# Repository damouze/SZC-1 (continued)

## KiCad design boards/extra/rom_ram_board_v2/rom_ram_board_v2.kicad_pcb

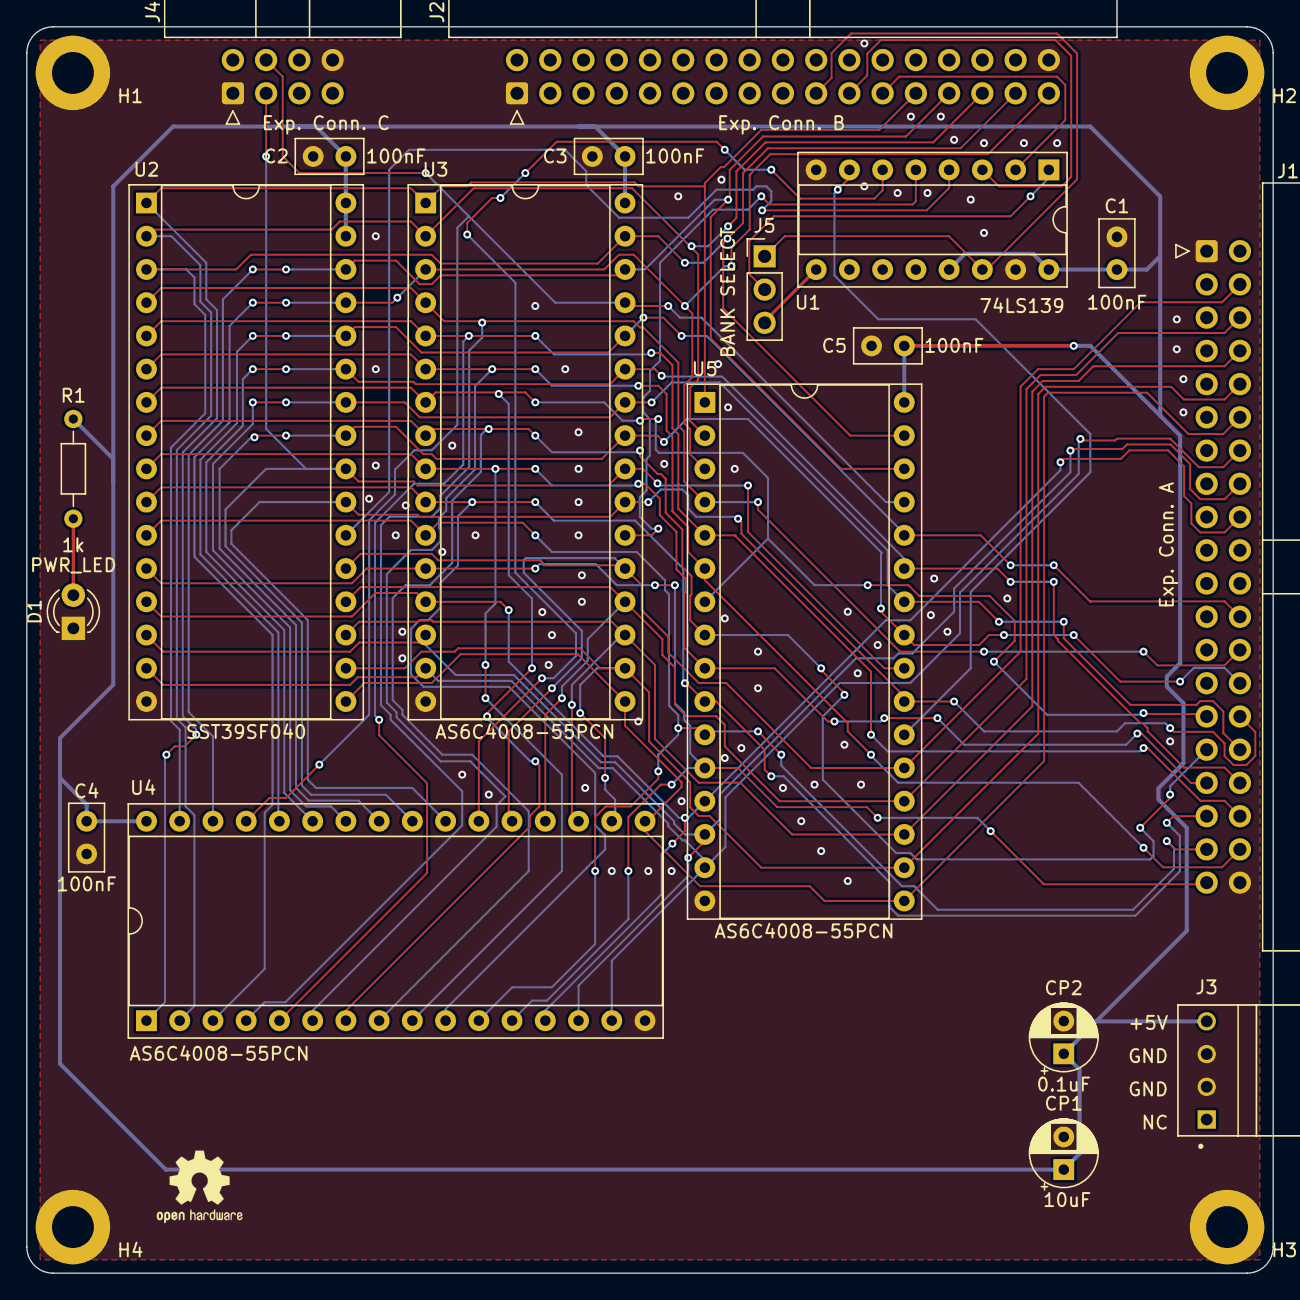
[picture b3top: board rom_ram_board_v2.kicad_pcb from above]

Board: 2 copper layers, 95.2 x 95.2 mm, 23 parts (0 on the bottom side), 41 nets.

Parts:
C1, C2, C3, C4, C5: 100nF; C_Disc_D5.0mm_W2.5mm_P2.50mm
CP1: 10uF; CP_Radial_D5.0mm_P2.50mm
CP2: 0.1uF; CP_Radial_D5.0mm_P2.50mm
D1: PWR_LED; LED_D3.0mm
H1, H2, H3, H4: MountingHole_Pad; MountingHole_3.2mm_M3_ISO7380_Pad
J1: Exp. Conn. A; IDC-Header_2x20_P2.54mm_Horizontal
J2: Exp. Conn. B; IDC-Header_2x17_P2.54mm_Horizontal
J3: Power; TE_171826-4
J4: Exp. Conn. C; IDC-Header_2x04_P2.54mm_Horizontal
J5: BANK SELECT; PinHeader_1x03_P2.54mm_Vertical
R1: 1k; R_Axial_DIN0204_L3.6mm_D1.6mm_P7.62mm_Horizontal
U1: 74LS139; DIP-16_W7.62mm_Socket
U2: SST39SF040; DIP-32_W15.24mm_Socket
U3, U4, U5: AS6C4008-55PCN; DIP-32_W15.24mm_Socket

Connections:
/+5V: C1.1, C2.1, C3.1, C4.1, C5.1, CP1.1, CP2.1, J3.4, R1.1, U1.13 (A1), U1.16 (VCC), U2.31 (PGM), U2.32 (VCC), U3.32 (VCC), U4.32 (VCC), U5.32 (VCC)
/B_A0: J1.39, U2.12 (A0), U3.12 (A0), U4.12 (A0), U5.12 (A0)
/B_A1: J1.37, U2.11 (A1), U3.11 (A1), U4.11 (A1), U5.11 (A1)
/B_A2: J1.35, U2.10 (A2), U3.10 (A2), U4.10 (A2), U5.10 (A2)
/B_A3: J1.33, U2.9 (A3), U3.9 (A3), U4.9 (A3), U5.9 (A3)
/B_A4: J1.31, U2.8 (A4), U3.8 (A4), U4.8 (A4), U5.8 (A4)
/B_A5: J1.29, U2.7 (A5), U3.7 (A5), U4.7 (A5), U5.7 (A5)
/B_A6: J1.38, U2.6 (A6), U3.6 (A6), U4.6 (A6), U5.6 (A6)
/B_A7: J1.36, U2.5 (A7), U3.5 (A7), U4.5 (A7), U5.5 (A7)
/B_A8: J1.34, U2.27 (A8), U3.27 (A8), U4.27 (A8), U5.27 (A8)
/B_A9: J1.32, U2.26 (A9), U3.26 (A9), U4.26 (A9), U5.26 (A9)
/B_A10: J1.30, U2.23 (A10), U3.23 (A10), U4.23 (A10), U5.23 (A10)
/B_A11: J1.28, U2.25 (A11), U3.25 (A11), U4.25 (A11), U5.25 (A11)
/B_A12: J1.26, U2.4 (A12), U3.4 (A12), U4.4 (A12), U5.4 (A12)
/B_A13: J1.24, U2.28 (A13), U3.28 (A13), U4.28 (A13), U5.28 (A13)
/B_D0: J1.18, U2.13 (D0), U3.13 (DQ0), U4.13 (DQ0), U5.13 (DQ0)
/B_D1: J1.16, U2.14 (D1), U3.14 (DQ1), U4.14 (DQ1), U5.14 (DQ1)
/B_D2: J1.14, U2.15 (D2), U3.15 (DQ2), U4.15 (DQ2), U5.15 (DQ2)
/B_D3: J1.12, U2.17 (D3), U3.17 (DQ3), U4.17 (DQ3), U5.17 (DQ3)
/B_D4: J1.10, U2.18 (D4), U3.18 (DQ4), U4.18 (DQ4), U5.18 (DQ4)
/B_D5: J1.8, U2.19 (D5), U3.19 (DQ5), U4.19 (DQ5), U5.19 (DQ5)
/B_D6: J1.6, U2.20 (D6), U3.20 (DQ6), U4.20 (DQ6), U5.20 (DQ6)
/B_D7: J1.4, U2.21 (D7), U3.21 (DQ7), U4.21 (DQ7), U5.21 (DQ7)
/GND: C1.2, C2.2, C3.2, C4.2, C5.2, CP1.2, CP2.2, D1.1 (K), H1.1, H2.1, H3.1, H4.1, J1.1, J1.40, J2.1, J2.34, J3.2, J3.3, J4.1, J4.8, U1.8 (GND), U1.15 (E), U2.16 (GND), U3.16 (VSS), U4.16 (VSS), U5.16 (VSS)
/M_A14: J2.33, U2.29 (A14), U3.3 (A14), U4.3 (A14), U5.3 (A14)
/M_A15: J2.31, U2.3 (A15), U3.31 (A15), U4.31 (A15), U5.31 (A15)
/M_A16: J2.29, U2.2 (A16), U3.2 (A16), U4.2 (A16), U5.2 (A16)
/M_A17: J2.27, U2.30 (A17), U3.30 (A17), U4.30 (A17), U5.30 (A17)
/M_A18: J2.25, U2.1 (A18), U3.1 (A18), U4.1 (A18), U5.1 (A18)
/M_A19: J2.23, U1.2 (A0)
/M_A20: J2.21, U1.3 (A1)
/M_A21: J2.19, J5.1, U1.14 (A0)
/~BANK_ENABLE: J5.2, U1.1 (E)
/~MA_21: J5.3, U1.9 (O3)
/~MEMR: J4.3, U2.24 (OE), U3.24 (OE#), U4.24 (OE#), U5.24 (OE#)
/~MEMW: J4.4, U3.29 (WE#), U4.29 (WE#), U5.29 (WE#)
/~MEM_CS1: U1.4 (O0), U2.22 (CE)
/~MEM_CS2: U1.5 (O1), U3.22 (CE#)
/~MEM_CS3: U1.6 (O2), U4.22 (CE#)
/~MEM_CS4: U1.7 (O3), U5.22 (CE#)
unnamed: D1.2 (A), R1.2

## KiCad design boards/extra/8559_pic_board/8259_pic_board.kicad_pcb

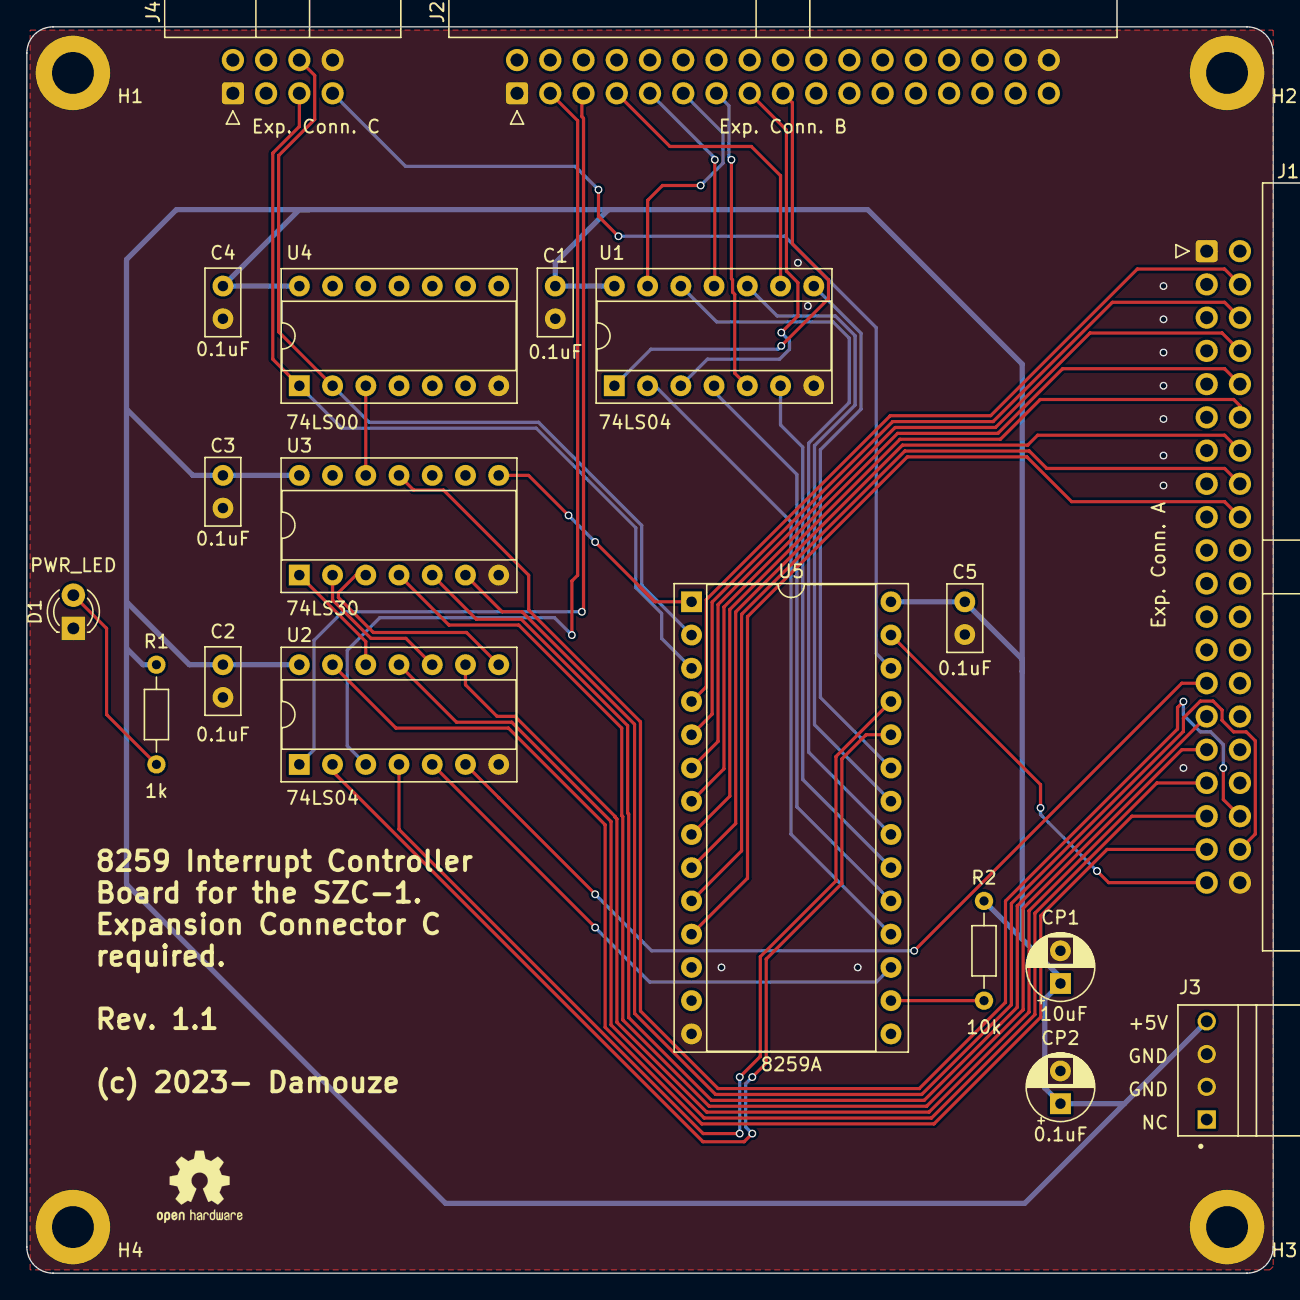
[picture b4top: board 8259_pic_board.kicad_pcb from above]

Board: 2 copper layers, 95.2 x 95.2 mm, 23 parts (0 on the bottom side), 46 nets.

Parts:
C1, C2, C3, C4, C5: 0.1uF; C_Disc_D5.0mm_W2.5mm_P2.50mm
CP1: 10uF; CP_Radial_D5.0mm_P2.50mm
CP2: 0.1uF; CP_Radial_D5.0mm_P2.50mm
D1: PWR_LED; LED_D3.0mm
H1, H2, H3, H4: MountingHole_Pad; MountingHole_3.2mm_M3_ISO7380_Pad
J1: Exp. Conn. A; IDC-Header_2x20_P2.54mm_Horizontal
J2: Exp. Conn. B; IDC-Header_2x17_P2.54mm_Horizontal
J3: Power; TE_171826-4
J4: Exp. Conn. C; IDC-Header_2x04_P2.54mm_Horizontal
R1: 1k; R_Axial_DIN0204_L3.6mm_D1.6mm_P7.62mm_Horizontal
R2: 10k; R_Axial_DIN0204_L3.6mm_D1.6mm_P7.62mm_Horizontal
U1, U2: 74LS04; DIP-14_W7.62mm_Socket
U3: 74LS30; DIP-14_W7.62mm_Socket
U4: 74LS00; DIP-14_W7.62mm_Socket
U5: 8259A; DIP-28_W15.24mm_Socket

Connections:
/+5V: C1.1, C2.1, C3.1, C4.1, C5.1, CP1.1, CP2.1, J3.4, R1.1, R2.2, U1.14 (VCC), U2.14 (VCC), U3.14 (VCC), U4.14 (VCC), U5.28 (VCC)
/B_A0: J1.39, U5.27 (A0)
/B_A1: J1.37, U2.13
/B_A2: J1.35, U2.11
/B_A3: J1.33, U2.9
/B_A4: J1.31, U3.4
/B_A5: J1.29, U3.5
/B_A6: J1.38, U3.6
/B_A7: J1.36, U3.11
/B_D0: J1.18, U5.11 (D0)
/B_D1: J1.16, U5.10 (D1)
/B_D2: J1.14, U5.9 (D2)
/B_D3: J1.12, U5.8 (D3)
/B_D4: J1.10, U5.7 (D4)
/B_D5: J1.8, U5.6 (D5)
/B_D6: J1.6, U5.5 (D6)
/B_D7: J1.4, U5.4 (D7)
/CPU_INT: U2.5, U5.17 (INT)
/GND: C1.2, C2.2, C3.2, C4.2, C5.2, CP1.2, CP2.2, D1.1 (K), H1.1, H2.1, H3.1, H4.1, J1.1, J1.40, J2.1, J2.34, J3.2, J3.3, J4.1, J4.8, U1.7 (GND), U2.7 (GND), U3.7 (GND), U4.7 (GND), U5.14 (GND)
/INT0: U1.2, U5.18 (IR0)
/INT1: U1.4, U5.19 (IR1)
/INT2: U1.6, U5.20 (IR2)
/INT3: U1.12, U5.21 (IR3)
/INT4: U1.10, U5.22 (IR4)
/INT5: U1.8, U5.23 (IR5)
/INT6: U2.2, U5.24 (IR6)
/INT7: U2.4, U5.25 (IR7)
/~BA_1: U2.12, U3.1
/~BA_2: U2.10, U3.2
/~BA_3: U2.8, U3.3
/~INT0: J2.17, U1.1
/~INT1: J2.15, U1.3
/~INT2: J2.13, U1.5
/~INT3: J2.11, U1.13
/~INT4: J2.9, U1.11
/~INT5: J2.7, U1.9
/~INT6: J2.5, U2.1
/~INT7: J2.3, U2.3
/~INTA: J4.7, U5.26 (~INTA)
/~INT: J1.27, U2.6
/~IOR: J4.5, U4.1, U5.3 (~RD)
/~IOW: J4.6, U4.2, U5.2 (~WR)
/~IOXS: U3.12, U4.3
/~PIC_CS: U3.8, U5.1 (~CS)
/~PIC_PLUP: R2.1, U5.16 (~SP/~EN)
unnamed: D1.2 (A), R1.2

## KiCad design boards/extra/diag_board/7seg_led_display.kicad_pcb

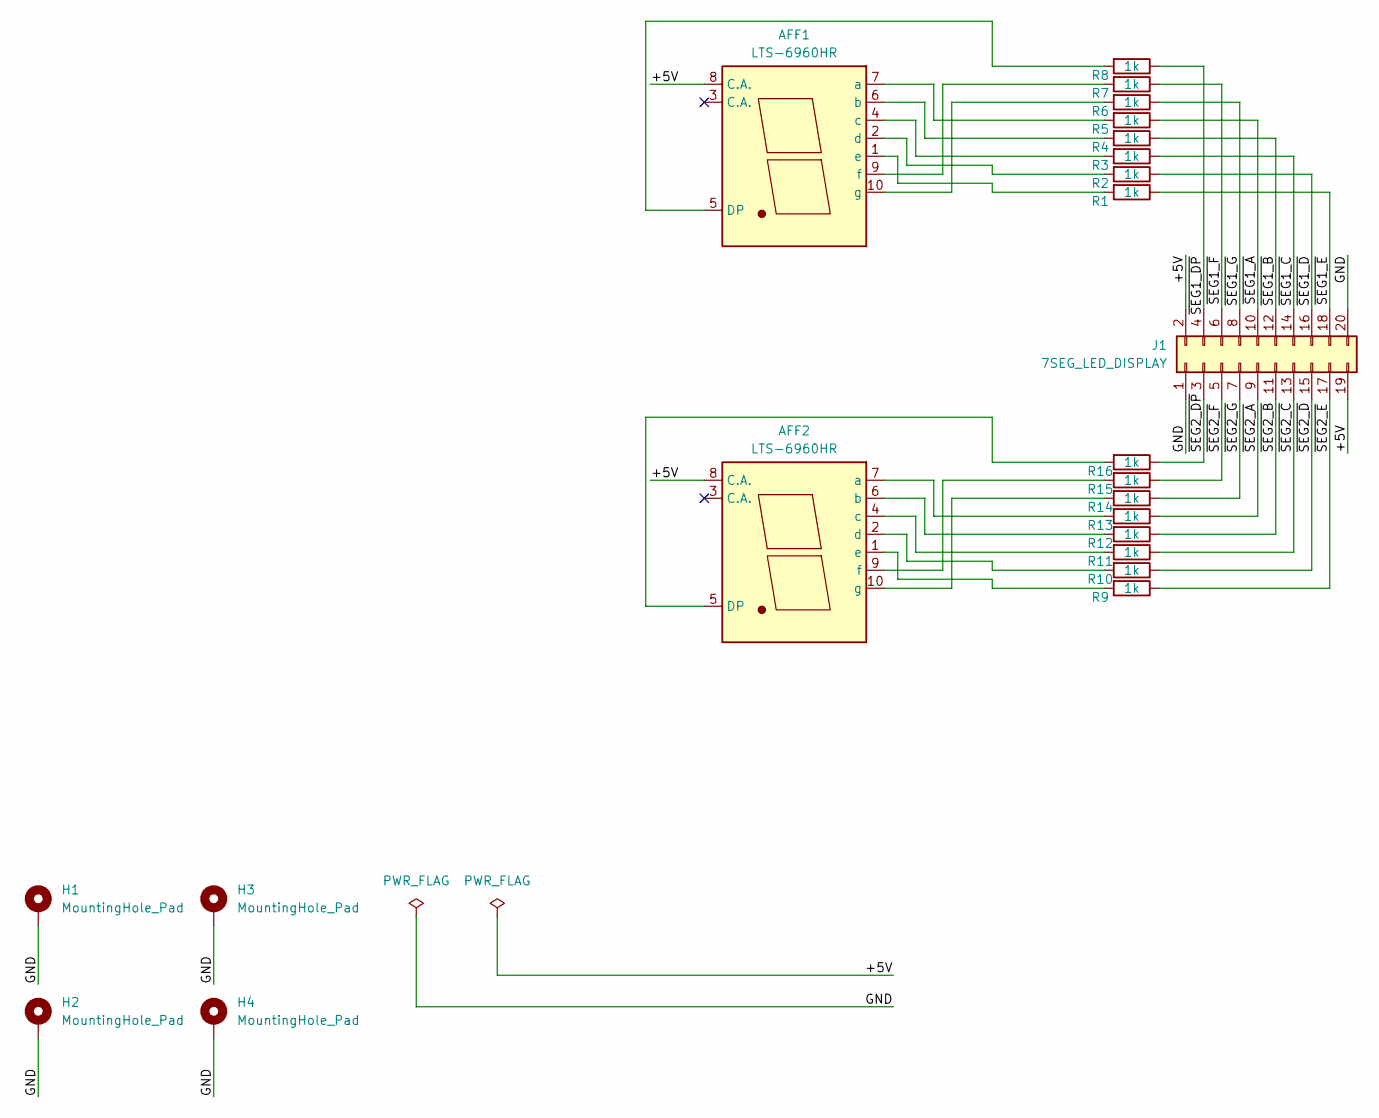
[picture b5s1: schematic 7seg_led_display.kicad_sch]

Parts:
AFF1, AFF2: LTS-6960HR; 7SegmentLED_LTS6760_LTS6780
H1, H2, H3, H4: MountingHole_Pad; MountingHole_3.2mm_M3_ISO7380_Pad
J1: 7SEG_LED_DISPLAY; PinSocket_2x10_P2.54mm_Vertical
R1, R2, R3, R4, R5, R6, R7, R8, R9, R10, R11, R12, R13, R14, R15, R16: 1k; R_Axial_DIN0204_L3.6mm_D1.6mm_P7.62mm_Horizontal

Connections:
/+5V: AFF1.8 (C.A.), AFF2.8 (C.A.), J1.2, J1.19
/GND: H1.1, H2.1, H3.1, H4.1, J1.1, J1.20
/~SEG1_A: J1.10, R5.1
/~SEG1_B: J1.12, R4.1
/~SEG1_C: J1.14, R3.1
/~SEG1_DP: J1.4, R8.1
/~SEG1_D: J1.16, R2.1
/~SEG1_E: J1.18, R1.1
/~SEG1_F: J1.6, R7.1
/~SEG1_G: J1.8, R6.1
/~SEG2_A: J1.9, R13.1
/~SEG2_B: J1.11, R12.1
/~SEG2_C: J1.13, R11.1
/~SEG2_DP: J1.3, R16.1
/~SEG2_D: J1.15, R10.1
/~SEG2_E: J1.17, R9.1
/~SEG2_F: J1.5, R15.1
/~SEG2_G: J1.7, R14.1
unnamed: AFF1.5 (DP), R8.2
unnamed: AFF1.7 (a), R5.2
unnamed: AFF1.6 (b), R4.2
unnamed: AFF1.4 (c), R3.2
unnamed: AFF1.2 (d), R2.2
unnamed: AFF1.1 (e), R1.2
unnamed: AFF1.9 (f), R7.2
unnamed: AFF1.10 (g), R6.2
unnamed: AFF2.5 (DP), R16.2
unnamed: AFF2.7 (a), R13.2
unnamed: AFF2.6 (b), R12.2
unnamed: AFF2.4 (c), R11.2
unnamed: AFF2.2 (d), R10.2
unnamed: AFF2.1 (e), R9.2
unnamed: AFF2.9 (f), R15.2
unnamed: AFF2.10 (g), R14.2

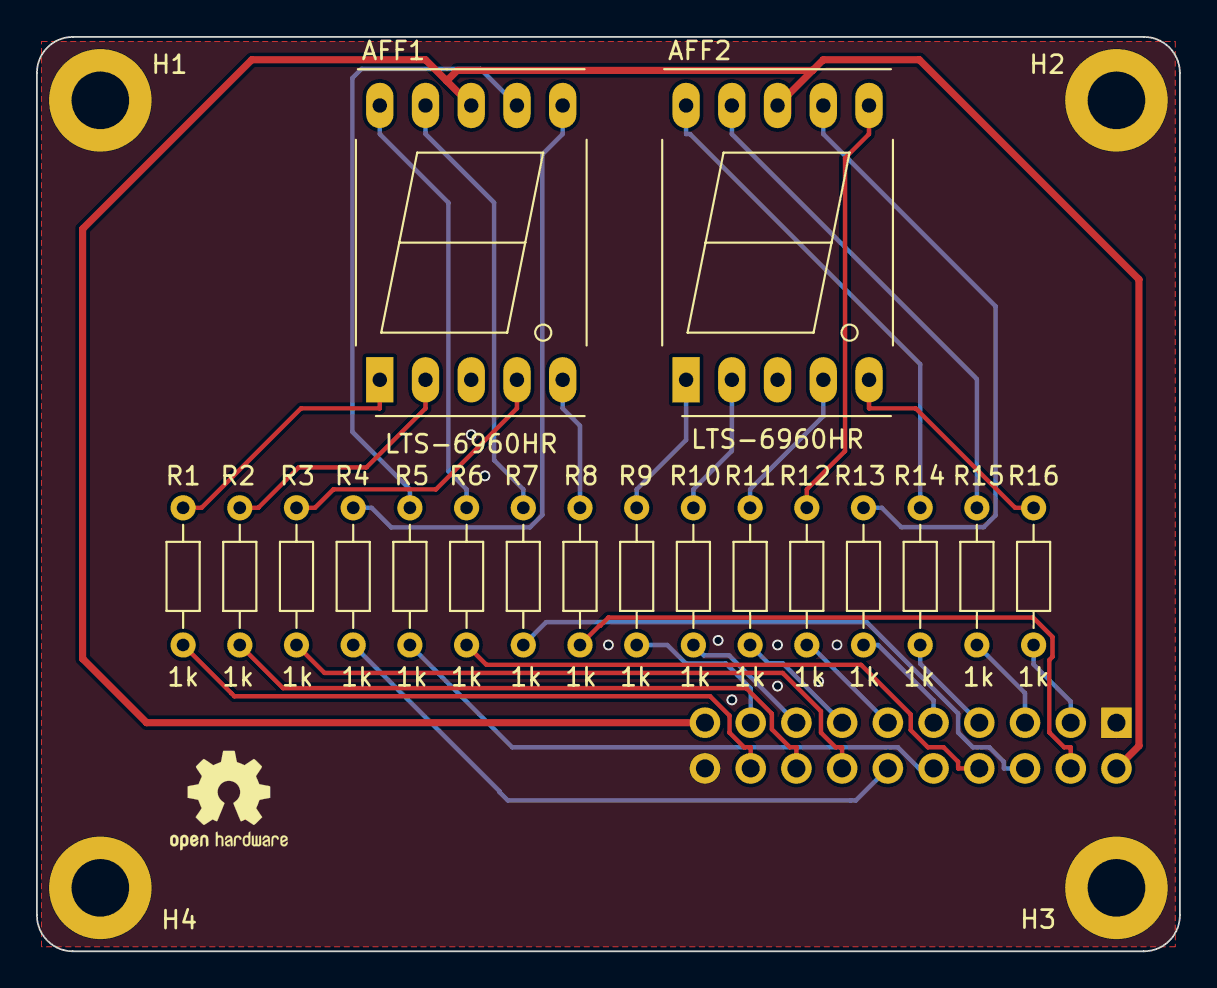
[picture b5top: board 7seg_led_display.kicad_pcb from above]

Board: 2 copper layers, 63.5 x 50.8 mm, 23 parts (1 on the bottom side), 34 nets.

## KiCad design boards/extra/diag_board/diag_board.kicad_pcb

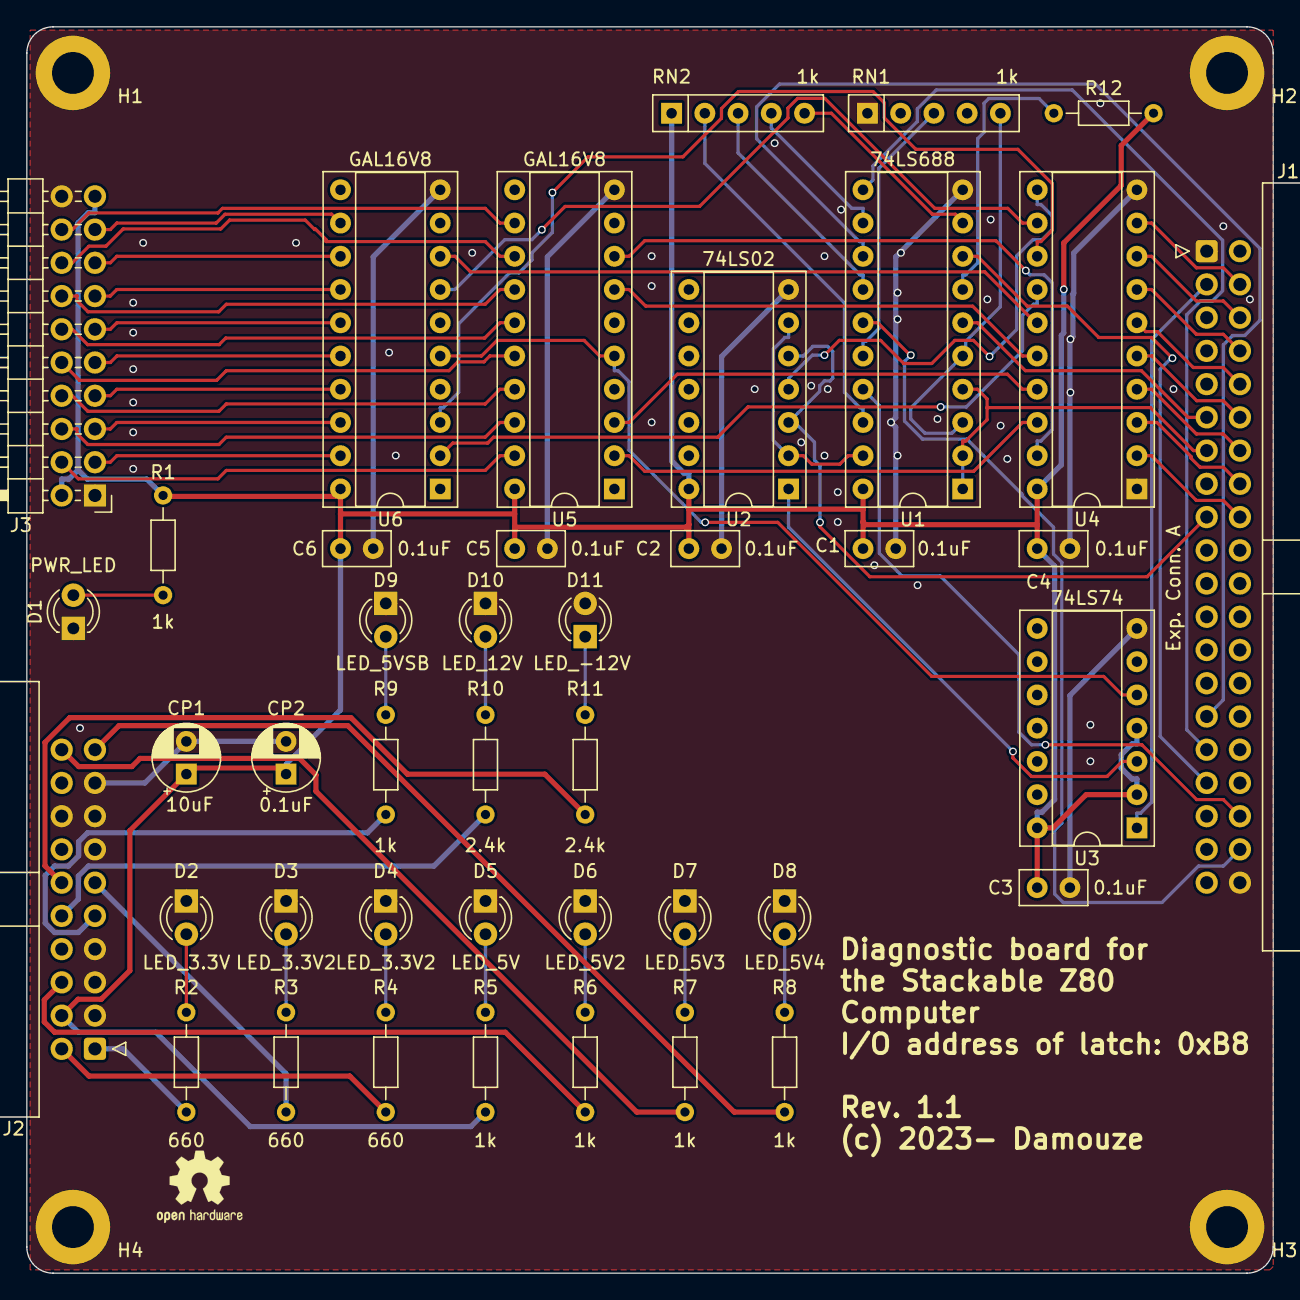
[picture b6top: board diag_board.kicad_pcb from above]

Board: 2 copper layers, 95.2 x 95.2 mm, 46 parts (0 on the bottom side), 74 nets.

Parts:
C1, C2, C3, C4, C5, C6: 0.1uF; C_Disc_D5.0mm_W2.5mm_P2.50mm
CP1: 10uF; CP_Radial_D5.0mm_P2.50mm
CP2: 0.1uF; CP_Radial_D5.0mm_P2.50mm
D1: PWR_LED; LED_D3.0mm
D2: LED_3.3V; LED_D3.0mm
D3, D4: LED_3.3V2; LED_D3.0mm
D5: LED_5V; LED_D3.0mm
D6: LED_5V2; LED_D3.0mm
D7: LED_5V3; LED_D3.0mm
D8: LED_5V4; LED_D3.0mm
D9: LED_5VSB; LED_D3.0mm
D10: LED_12V; LED_D3.0mm
D11: LED_-12V; LED_D3.0mm
H1, H2, H3, H4: MountingHole_Pad; MountingHole_3.2mm_M3_ISO7380_Pad
J1: Exp. Conn. A; IDC-Header_2x20_P2.54mm_Horizontal
J2: Power; IDC-Header_2x10_P2.54mm_Horizontal
J3: 7SEG_LED_DISPLAY; PinHeader_2x10_P2.54mm_Horizontal
R1, R5, R6, R7, R8, R9, R12: 1k; R_Axial_DIN0204_L3.6mm_D1.6mm_P7.62mm_Horizontal
R2, R3, R4: 660; R_Axial_DIN0204_L3.6mm_D1.6mm_P7.62mm_Horizontal
R10, R11: 2.4k; R_Axial_DIN0204_L3.6mm_D1.6mm_P7.62mm_Horizontal
RN1, RN2: 1k; R_Array_SIP5
U1: 74LS688; DIP-20_W7.62mm_Socket
U2: 74LS02; DIP-14_W7.62mm_Socket
U3: 74LS74; DIP-14_W7.62mm_Socket
U4: 74LS573; DIP-20_W7.62mm_Socket
U5, U6: GAL16V8; DIP-20_W7.62mm_Socket

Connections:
/+3.3V: J2.1, R2.1
/+3.3V2: J2.2, R4.1
/+3.3V3: J2.11, R3.1
/+5V: C1.1, C2.1, C3.1, C4.1, C5.1, C6.1, CP1.1, CP2.1, J2.4, J3.2, J3.19, R1.1, R5.1, R12.2, RN2.1 (common), U1.20 (VCC), U2.14 (VCC), U3.2 (D), U3.4 (~S), U3.14 (VCC), U4.20 (VCC), U5.20 (VCC), U6.20 (VCC)
/+5V2: J2.6, R6.1
/+5V3: J2.20, R7.1
/+5V4: J2.19, R8.1
/+5VSB: J2.9, R9.1
/+12V: J2.10, R10.1
/-12V: J2.12, R11.1
/B_A3: J1.33, U1.8 (P3)
/B_A4: J1.31, U1.11 (P4)
/B_A5: J1.29, U1.13 (P5)
/B_A6: J1.38, U1.15 (P6)
/B_A7: J1.36, U1.17 (P7)
/B_D0: J1.18, U4.2 (D0)
/B_D1: J1.16, U4.3 (D1)
/B_D2: J1.14, U4.4 (D2)
/B_D3: J1.12, U4.5 (D3)
/B_D4: J1.10, U4.6 (D4)
/B_D5: J1.8, U4.7 (D5)
/B_D6: J1.6, U4.8 (D6)
/B_D7: J1.4, U4.9 (D7)
/DIAG_CS: U2.4, U4.11 (Load)
/GND: C1.2, C2.2, C3.2, C4.2, C5.2, C6.2, CP1.2, CP2.2, D1.1 (K), D2.1 (K), D3.1 (K), D4.1 (K), D5.1 (K), D6.1 (K), D7.1 (K), D8.1 (K), D9.1 (K), D10.1 (K), D11.2 (A), H1.1, H2.1, H3.1, H4.1, J1.1, J1.40, J2.3, J2.5, J2.7, J2.13, J2.15, J2.16, J2.17, J3.1, J3.20, RN1.1 (common), U1.10 (GND), U2.7 (GND), U3.7 (GND), U4.1 (OE), U4.10 (GND), U5.10 (GND), U6.10 (GND)
/I0: U4.19 (Q0), U5.8 (I8)
/I1: U4.18 (Q1), U5.2 (I2)
/I2: U4.17 (Q2), U5.3 (I3)
/I3: U4.16 (Q3), U5.7 (I7)
/I4: U4.15 (Q4), U6.8 (I8)
/I5: U4.14 (Q5), U6.2 (I2)
/I6: U4.13 (Q6), U6.3 (I3)
/I7: U4.12 (Q7), U6.7 (I7)
/L_CLK: U2.1, U3.3 (C)
/R_A3: RN2.5 (R4), U1.9 (R3)
/R_A4: RN2.4 (R3), U1.12 (R4)
/R_A5: RN2.3 (R2), U1.14 (R5)
/R_A6: RN1.3 (R2), U1.16 (R6)
/R_A7: RN2.2 (R1), U1.18 (R7)
/~BI: U3.5 (Q), U5.5 (I5), U6.5 (I5)
/~B_IORQ: J1.13, U1.1 (G), U1.2 (P0), U1.4 (P1)
/~B_M1: J1.11, U1.6 (P2)
/~B_WR: J1.17, U2.3, U2.5
/~DIAG_CS: U1.19 (P=R), U2.2, U2.6
/~RESET: J1.3, U3.1 (~R)
/~R_IORQ: RN1.5 (R4), U1.3 (R0), U1.5 (R1)
/~R_M1: R12.1, U1.7 (R2)
/~SEG1_A: J3.10, U5.16 (IO4)
/~SEG1_B: J3.12, U5.15 (IO5)
/~SEG1_C: J3.14, U5.14 (IO6)
/~SEG1_DP: J3.4, U5.19 (IO1)
/~SEG1_D: J3.16, U5.13 (IO7)
/~SEG1_E: J3.18, U5.12 (IO8)
/~SEG1_F: J3.6, U5.18 (IO2)
/~SEG1_G: J3.8, U5.17 (I03)
/~SEG2_A: J3.9, U6.16 (IO4)
/~SEG2_B: J3.11, U6.15 (IO5)
/~SEG2_C: J3.13, U6.14 (IO6)
/~SEG2_DP: J3.3, U6.19 (IO1)
/~SEG2_D: J3.15, U6.13 (IO7)
/~SEG2_E: J3.17, U6.12 (IO8)
/~SEG2_F: J3.5, U6.18 (IO2)
/~SEG2_G: J3.7, U6.17 (I03)
unnamed: D1.2 (A), R1.2
unnamed: D2.2 (A), R2.2
unnamed: D3.2 (A), R3.2
unnamed: D4.2 (A), R4.2
unnamed: D5.2 (A), R5.2
unnamed: D6.2 (A), R6.2
unnamed: D7.2 (A), R7.2
unnamed: D8.2 (A), R8.2
unnamed: D9.2 (A), R9.2
unnamed: D10.2 (A), R10.2
unnamed: D11.1 (K), R11.2

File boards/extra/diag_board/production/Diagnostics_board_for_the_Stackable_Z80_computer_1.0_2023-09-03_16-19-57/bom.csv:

Designator,Footprint,Quantity,Value,LCSC Part #
"C1, C2, C3, C4, C5, C6, C7",C_Disc_D5.0mm_W2.5mm_P2.50mm,7,0.1uF,
CP1,CP_Radial_D5.0mm_P2.50mm,1,10uF,
CP2,CP_Radial_D5.0mm_P2.50mm,1,0.1uF,
D1,LED_D3.0mm,1,PWR_LED,
D10,LED_D3.0mm,1,LED_12V,
D11,LED_D3.0mm,1,LED_-12V,
D2,LED_D3.0mm,1,LED_3.3V,
"D3, D4",LED_D3.0mm,2,LED_3.3V2,
D5,LED_D3.0mm,1,LED_5V,
D6,LED_D3.0mm,1,LED_5V2,
D7,LED_D3.0mm,1,LED_5V3,
D8,LED_D3.0mm,1,LED_5V4,
D9,LED_D3.0mm,1,LED_5VSB,
"H1, H2, H3, H4",MountingHole_3.2mm_M3_ISO7380_Pad,4,MountingHole_Pad,
J1,IDC-Header_2x20_P2.54mm_Horizontal,1,Exp. Conn. A,
J3,IDC-Header_2x10_P2.54mm_Horizontal,1,Power,
J4,PinHeader_2x10_P2.54mm_Horizontal,1,7SEG_LED_DISPLAY,
R1,R_Axial_DIN0204_L3.6mm_D1.6mm_P7.62mm_Horizontal,1,470,
"R10, R11",R_Axial_DIN0204_L3.6mm_D1.6mm_P7.62mm_Horizontal,2,2.4k,
"R2, R3, R4",R_Axial_DIN0204_L3.6mm_D1.6mm_P7.62mm_Horizontal,3,660,
"R5, R6, R7, R8, R9",R_Axial_DIN0204_L3.6mm_D1.6mm_P7.62mm_Horizontal,5,1k,
"RN1, RN2",R_Array_SIP5,2,1k,
U1,DIP-20_W7.62mm_Socket,1,74LS688,
U2,DIP-14_W7.62mm_Socket,1,74LS04,
U3,DIP-14_W7.62mm_Socket,1,74LS74,
U4,DIP-14_W7.62mm_Socket,1,74LS02,
U5,DIP-20_W7.62mm_Socket,1,74LS573,
"U6, U7",DIP-20_W7.62mm_Socket,2,GAL16V8,

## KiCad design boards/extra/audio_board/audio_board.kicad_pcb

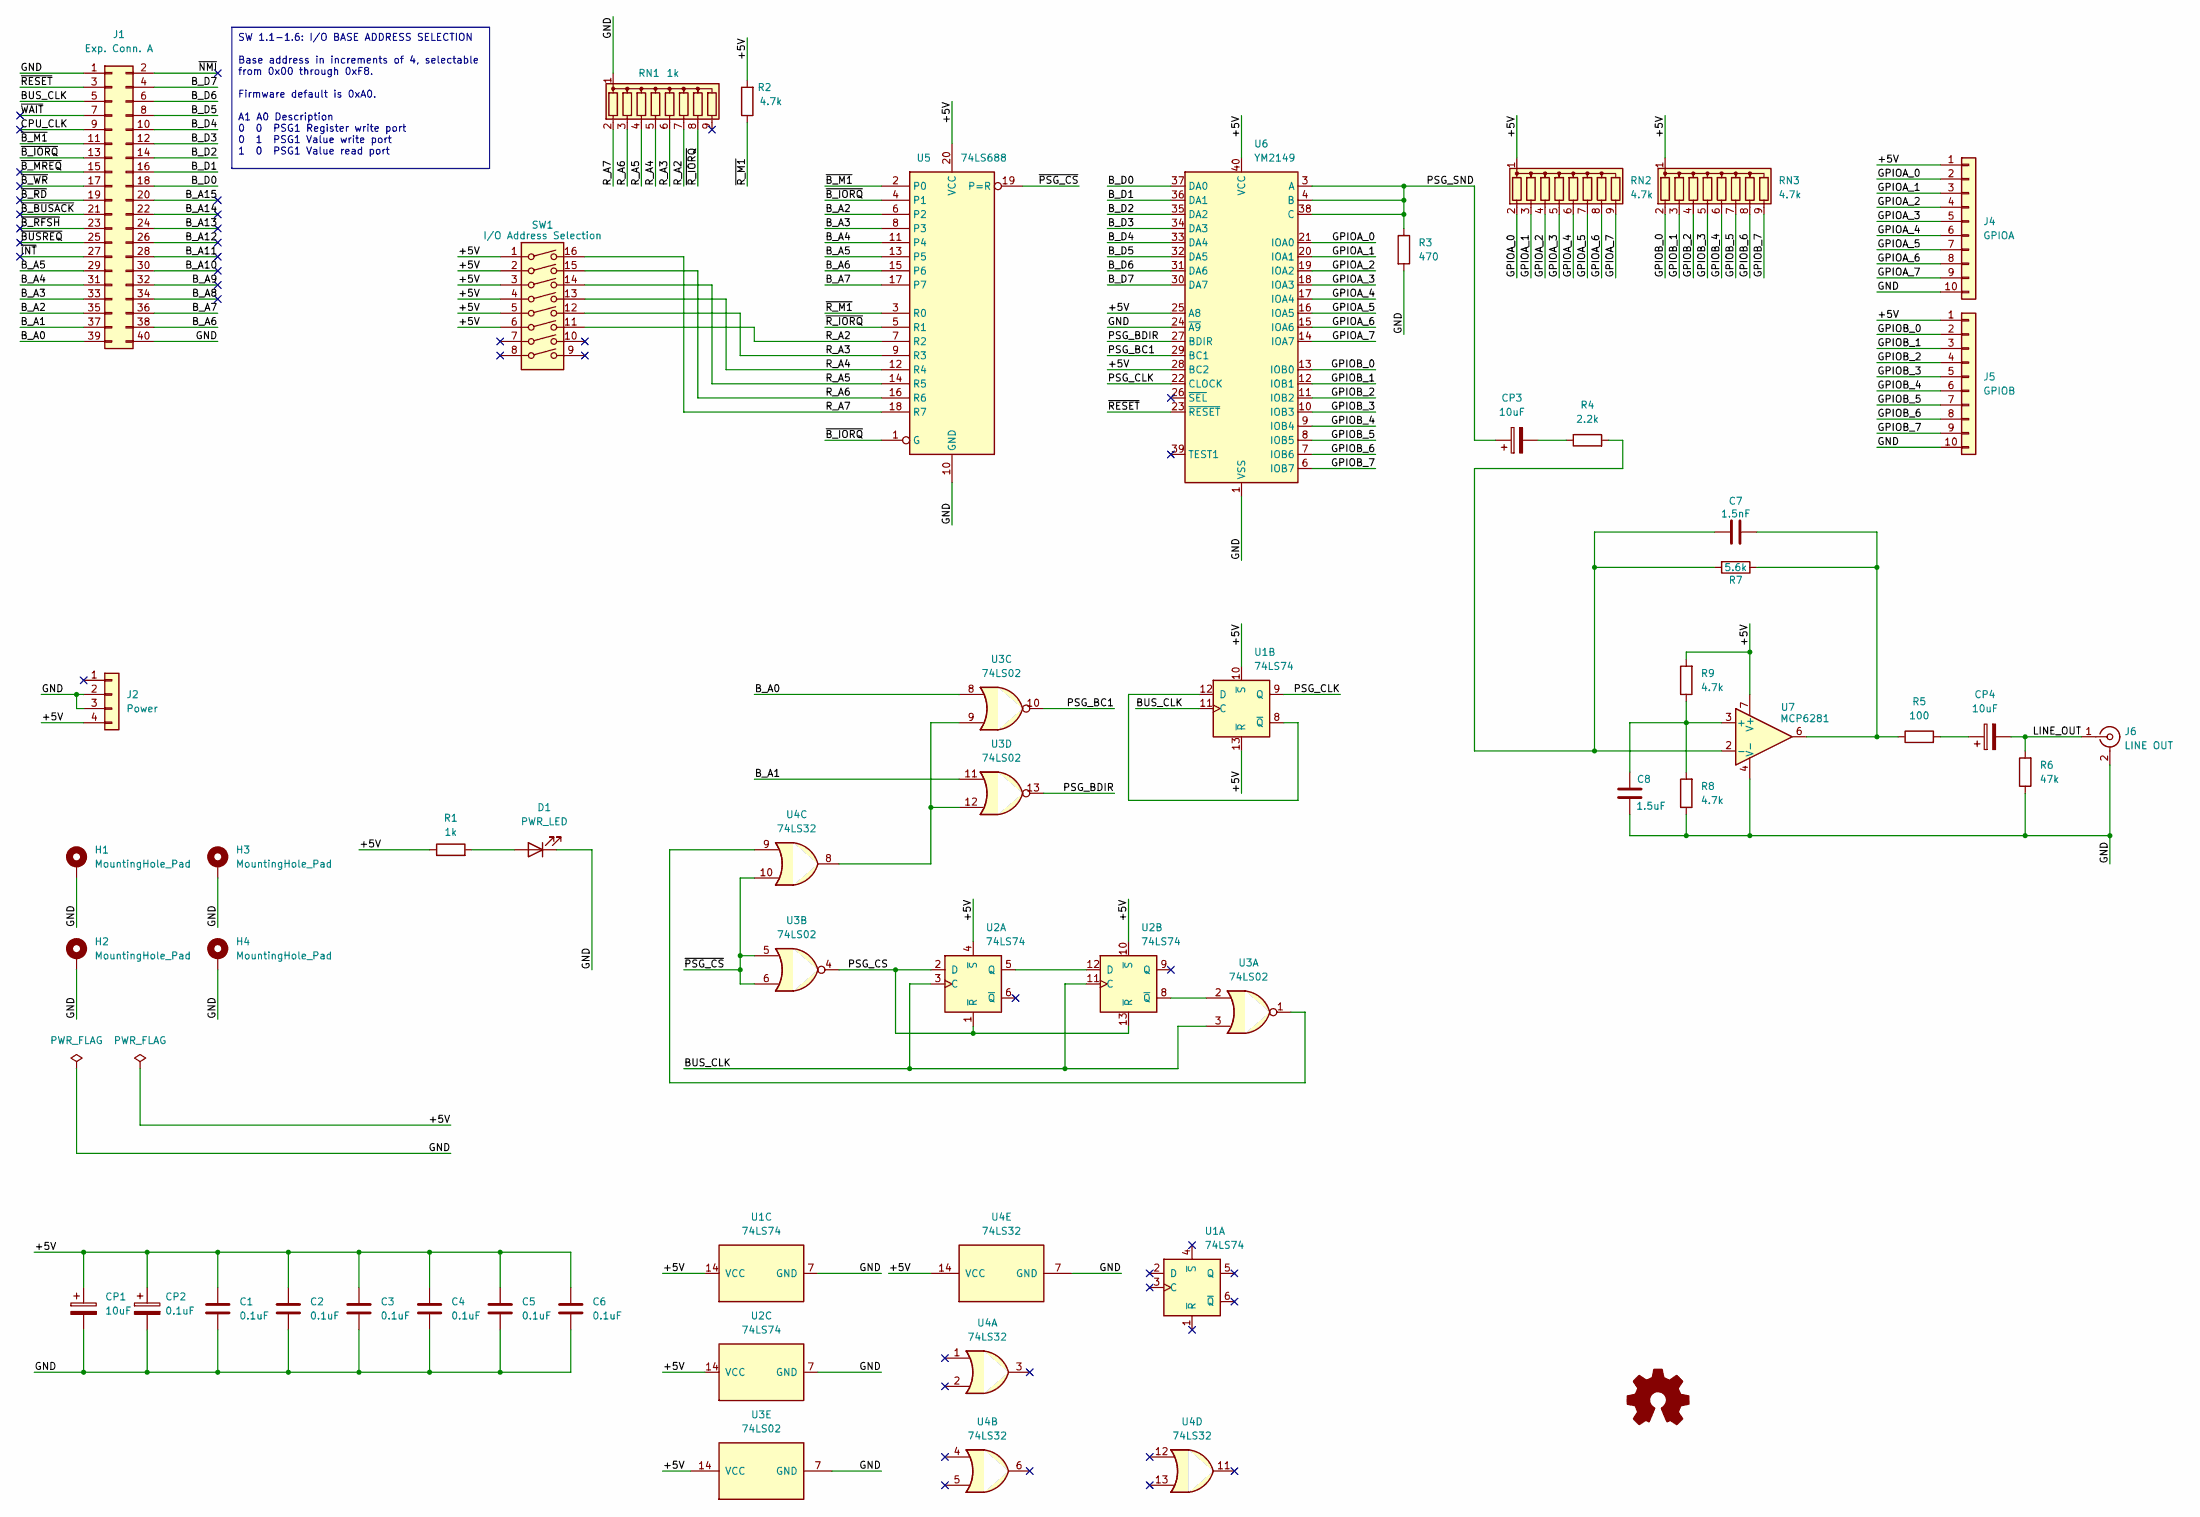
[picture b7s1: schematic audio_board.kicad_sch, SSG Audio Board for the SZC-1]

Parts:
C1, C2, C3, C4, C5, C6: 0.1uF; C_Disc_D5.0mm_W2.5mm_P2.50mm
C7: 1.5nF; C_Axial_L3.8mm_D2.6mm_P7.50mm_Horizontal
C8: 1.5uF; C_Axial_L3.8mm_D2.6mm_P7.50mm_Horizontal
CP1, CP3, CP4: 10uF; CP_Radial_D5.0mm_P2.50mm
CP2: 0.1uF; CP_Radial_D5.0mm_P2.50mm
D1: PWR_LED; LED_D3.0mm
H1, H2, H3, H4: MountingHole_Pad; MountingHole_3.2mm_M3_ISO7380_Pad
J1: Exp. Conn. A; IDC-Header_2x20_P2.54mm_Horizontal
J2: Power; TE_171826-4
J4: GPIOA; PinSocket_1x10_P2.54mm_Horizontal
J5: GPIOB; PinSocket_1x10_P2.54mm_Horizontal
J6: LINE OUT; CUI_RCJ-041
R1: 1k; R_Axial_DIN0204_L3.6mm_D1.6mm_P7.62mm_Horizontal
R2, R8, R9: 4.7k; R_Axial_DIN0204_L3.6mm_D1.6mm_P7.62mm_Horizontal
R3: 470; R_Axial_DIN0204_L3.6mm_D1.6mm_P7.62mm_Horizontal
R4: 2.2k; R_Axial_DIN0204_L3.6mm_D1.6mm_P7.62mm_Horizontal
R5: 100; R_Axial_DIN0204_L3.6mm_D1.6mm_P7.62mm_Horizontal
R6: 47k; R_Axial_DIN0204_L3.6mm_D1.6mm_P7.62mm_Horizontal
R7: 5.6k; R_Axial_DIN0204_L3.6mm_D1.6mm_P7.62mm_Horizontal
RN1: 1k; R_Array_SIP9
RN2, RN3: 4.7k; R_Array_SIP9
SW1: I/O Address Selection; SW_DIP_SPSTx08_Slide_6.7x21.88mm_W7.62mm_P2.54mm_LowProfile
U1, U2: 74LS74; DIP-14_W7.62mm_Socket
U3: 74LS02; DIP-14_W7.62mm_Socket
U4: 74LS32; DIP-14_W7.62mm_Socket
U5: 74LS688; DIP-20_W7.62mm_Socket
U6: YM2149; DIP-40_W15.24mm_Socket
U7: MCP6281; DIP-8_W7.62mm_Socket

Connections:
/+5V: C1.1, C2.1, C3.1, C4.1, C5.1, C6.1, CP1.1, CP2.1, J2.4, J4.1, J5.1, R1.1, R2.2, R9.2, RN2.1 (common), RN3.1 (common), SW1.1, SW1.2, SW1.3, SW1.4, SW1.5, SW1.6, U1.10 (~S), U1.13 (~R), U1.14 (VCC), U2.4 (~S), U2.10 (~S), U2.14 (VCC), U3.14 (VCC), U4.14 (VCC), U5.20 (VCC), U6.25 (A8), U6.28 (BC2), U6.40 (VCC), U7.7 (V+)
/BUS_CLK: J1.5, U1.11 (C), U2.3 (C), U2.11 (C), U3.3
/B_A0: J1.39, U3.8
/B_A1: J1.37, U3.11
/B_A2: J1.35, U5.6 (P2)
/B_A3: J1.33, U5.8 (P3)
/B_A4: J1.31, U5.11 (P4)
/B_A5: J1.29, U5.13 (P5)
/B_A6: J1.38, U5.15 (P6)
/B_A7: J1.36, U5.17 (P7)
/B_A8: J1.34
/B_A9: J1.32
/B_A10: J1.30
/B_A11: J1.28
/B_A12: J1.26
/B_A13: J1.24
/B_A14: J1.22
/B_A15: J1.20
/B_D0: J1.18, U6.37 (DA0)
/B_D1: J1.16, U6.36 (DA1)
/B_D2: J1.14, U6.35 (DA2)
/B_D3: J1.12, U6.34 (DA3)
/B_D4: J1.10, U6.33 (DA4)
/B_D5: J1.8, U6.32 (DA5)
/B_D6: J1.6, U6.31 (DA6)
/B_D7: J1.4, U6.30 (DA7)
/CPU_CLK: J1.9
/GND: C1.2, C2.2, C3.2, C4.2, C5.2, C6.2, C8.1, CP1.2, CP2.2, D1.1 (K), H1.1, H2.1, H3.1, H4.1, J1.1, J1.40, J2.2, J2.3, J4.10, J5.10, J6.2 (Ext), R3.2, R6.1, R8.1, RN1.1 (common), U1.7 (GND), U2.7 (GND), U3.7 (GND), U4.7 (GND), U5.10 (GND), U6.1 (VSS), U6.24 (~A9), U7.4 (V-)
/GPIOA_0: J4.2, RN2.2 (R1), U6.21 (IOA0)
/GPIOA_1: J4.3, RN2.3 (R2), U6.20 (IOA1)
/GPIOA_2: J4.4, RN2.4 (R3), U6.19 (IOA2)
/GPIOA_3: J4.5, RN2.5 (R4), U6.18 (IOA3)
/GPIOA_4: J4.6, RN2.6 (R5), U6.17 (IOA4)
/GPIOA_5: J4.7, RN2.7 (R6), U6.16 (IOA5)
/GPIOA_6: J4.8, RN2.8 (R7), U6.15 (IOA6)
/GPIOA_7: J4.9, RN2.9 (R8), U6.14 (IOA7)
/GPIOB_0: J5.2, RN3.2 (R1), U6.13 (IOB0)
/GPIOB_1: J5.3, RN3.3 (R2), U6.12 (IOB1)
/GPIOB_2: J5.4, RN3.4 (R3), U6.11 (IOB2)
/GPIOB_3: J5.5, RN3.5 (R4), U6.10 (IOB3)
/GPIOB_4: J5.6, RN3.6 (R5), U6.9 (IOB4)
/GPIOB_5: J5.7, RN3.7 (R6), U6.8 (IOB5)
/GPIOB_6: J5.8, RN3.8 (R7), U6.7 (IOB6)
/GPIOB_7: J5.9, RN3.9 (R8), U6.6 (IOB7)
/LINE_OUT: CP4.2, J6.1 (In), R6.2
/PSG_BC1: U3.10, U6.29 (BC1)
/PSG_BDIR: U3.13, U6.27 (BDIR)
/PSG_CLK: U1.9 (Q), U6.22 (CLOCK)
/PSG_CS: U2.1 (~R), U2.2 (D), U2.13 (~R), U3.4
/PSG_SND: CP3.1, R3.1, U6.3 (A), U6.4 (B), U6.38 (C)
/R_A2: RN1.7 (R6), SW1.11, U5.7 (R2)
/R_A3: RN1.6 (R5), SW1.12, U5.9 (R3)
/R_A4: RN1.5 (R4), SW1.13, U5.12 (R4)
/R_A5: RN1.4 (R3), SW1.14, U5.14 (R5)
/R_A6: RN1.3 (R2), SW1.15, U5.16 (R6)
/R_A7: RN1.2 (R1), SW1.16, U5.18 (R7)
/~BUSREQ: J1.25
/~B_BUSACK: J1.21
/~B_IORQ: J1.13, U5.1 (G), U5.4 (P1)
/~B_M1: J1.11, U5.2 (P0)
/~B_MREQ: J1.15
/~B_RD: J1.19
/~B_RFSH: J1.23
/~B_WR: J1.17
/~INT: J1.27
/~NMI: J1.2
/~PSG_CS: U3.5, U3.6, U4.10, U5.19 (P=R)
/~RESET: J1.3, U6.23 (~RESET)
/~R_IORQ: RN1.8 (R7), U5.5 (R1)
/~R_M1: R2.1, U5.3 (R0)
/~WAIT: J1.7
unnamed: C7.1, R5.1, R7.1, U7.6
unnamed: CP3.2, R4.1
unnamed: CP4.1, R5.2
unnamed: D1.2 (A), R1.2
unnamed: U1.8 (~Q), U1.12 (D)
unnamed: U2.5 (Q), U2.12 (D)
unnamed: U2.8 (~Q), U3.2
unnamed: U3.1, U4.9
unnamed: U3.9, U3.12, U4.8
unnamed: C8.2, R8.2, R9.1, U7.3 (+)
unnamed: C7.2, R4.2, R7.2, U7.2 (-)

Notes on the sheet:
SW 1.1-1.6: I/O BASE ADDRESS SELECTION Base address in increments of 4, selectable from 0x00 through 0xF8. Firmware default is 0xA0. A1 A0 Description 0 0 PSG1 Register write port 0 1 PSG1 Value write port 1 0 PSG1 Value read port

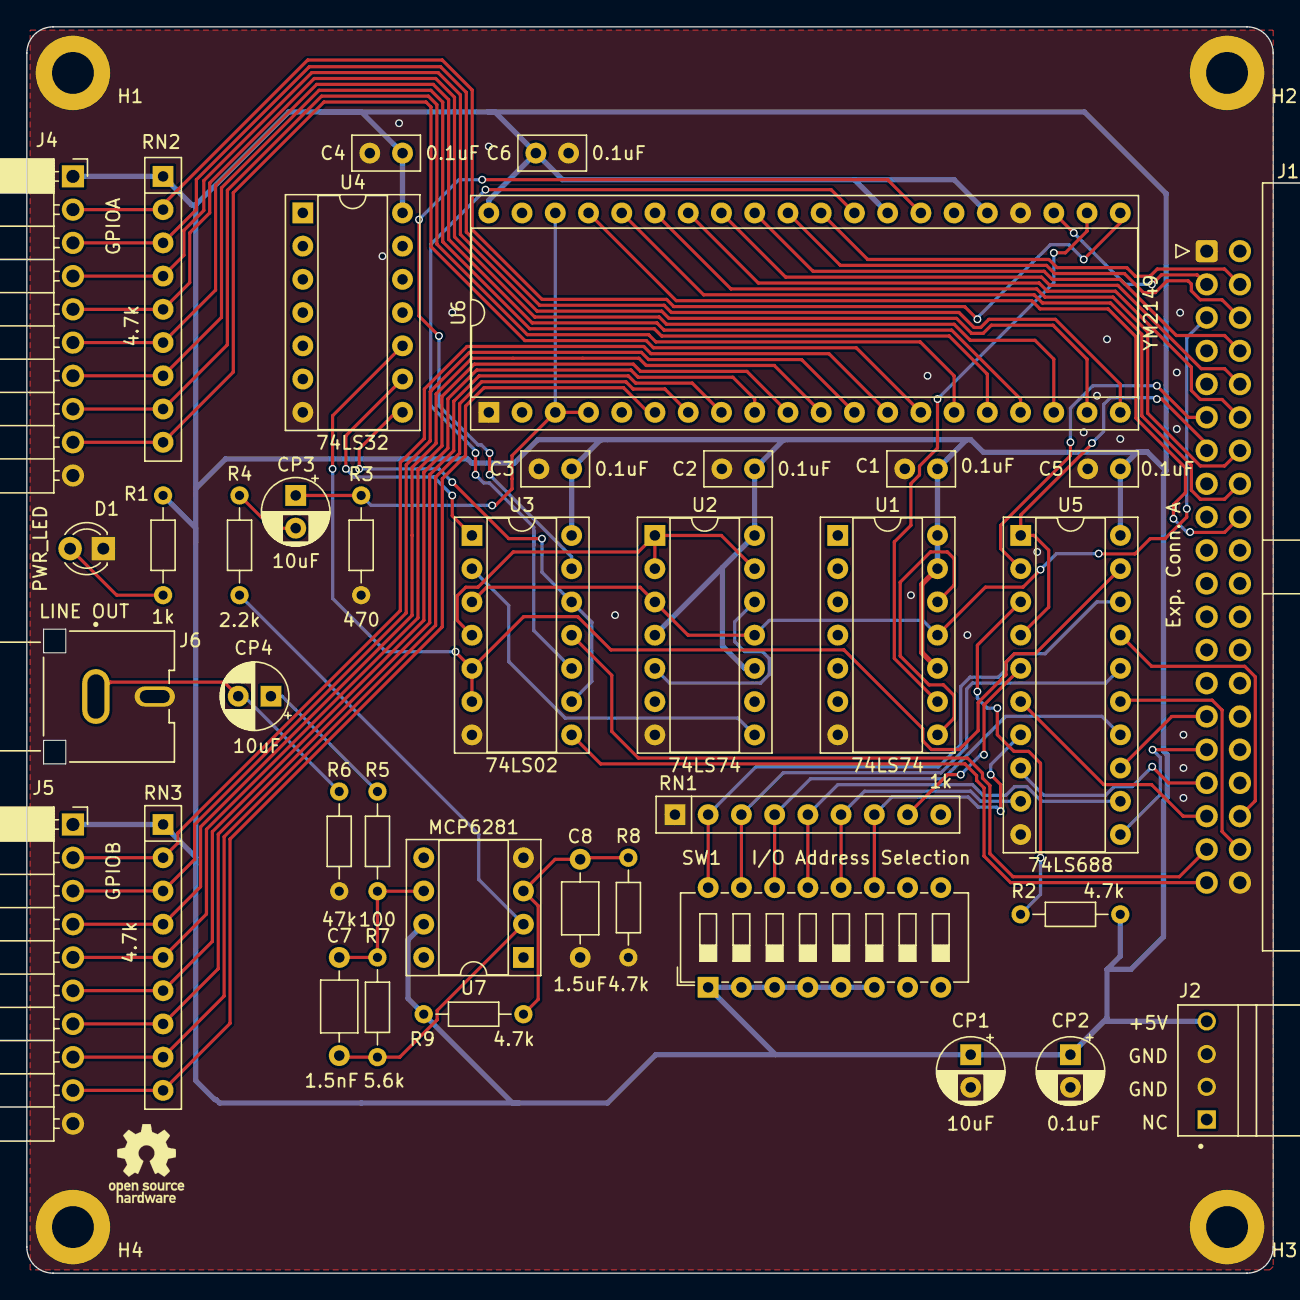
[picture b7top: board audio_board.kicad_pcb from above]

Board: 2 copper layers, 95.2 x 95.2 mm, 42 parts (0 on the bottom side), 64 nets.
